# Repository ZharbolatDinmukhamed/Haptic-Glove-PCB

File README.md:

# Haptic Glove PCB

A wrist-mounted PCB for a haptic feedback glove, developed as part of my Research Assistantship at the Tactile Laboratory, Nazarbayev University.

## Overview
The board mounts on the wrist and drives 5 vibromotors, one per fingertip, delivering independent tactile feedback to each finger. It is designed to sit inside a glove, secured to the wrist via velcro straps threaded through slots in the board.

## Design Details
- **Board size:** 65mm x 50mm
- **Actuators:** 5x vibromotors (one per fingertip), each with a dedicated 3.3V power channel and signal channel
- **Driver components:** Capacitors and diodes placed near the board edge for each motor driver channel
- **Wrist-to-fingertip connection:** Discrete flexible wire harness (evaluated flex PCB / FPC, but chose a wire harness for flexibility and cost)
- **Mounting:** Component side faces outward (away from skin); board sits on the palm/volar side of the wrist inside the glove
- **Hand coverage:** Single-hand design

## Files
- `/schematic` — Schematic source files
- `/pcb` — PCB layout files
- `/gerbers` — Fabrication-ready Gerber files
- `/images` — Board renders and assembled photos
- `BOM.csv` — Bill of materials

## Tools
- [Your EDA tool — e.g. KiCad / Altium / Eagle]

## Status
[In progress / Fabricated & tested / etc. — update with current status]

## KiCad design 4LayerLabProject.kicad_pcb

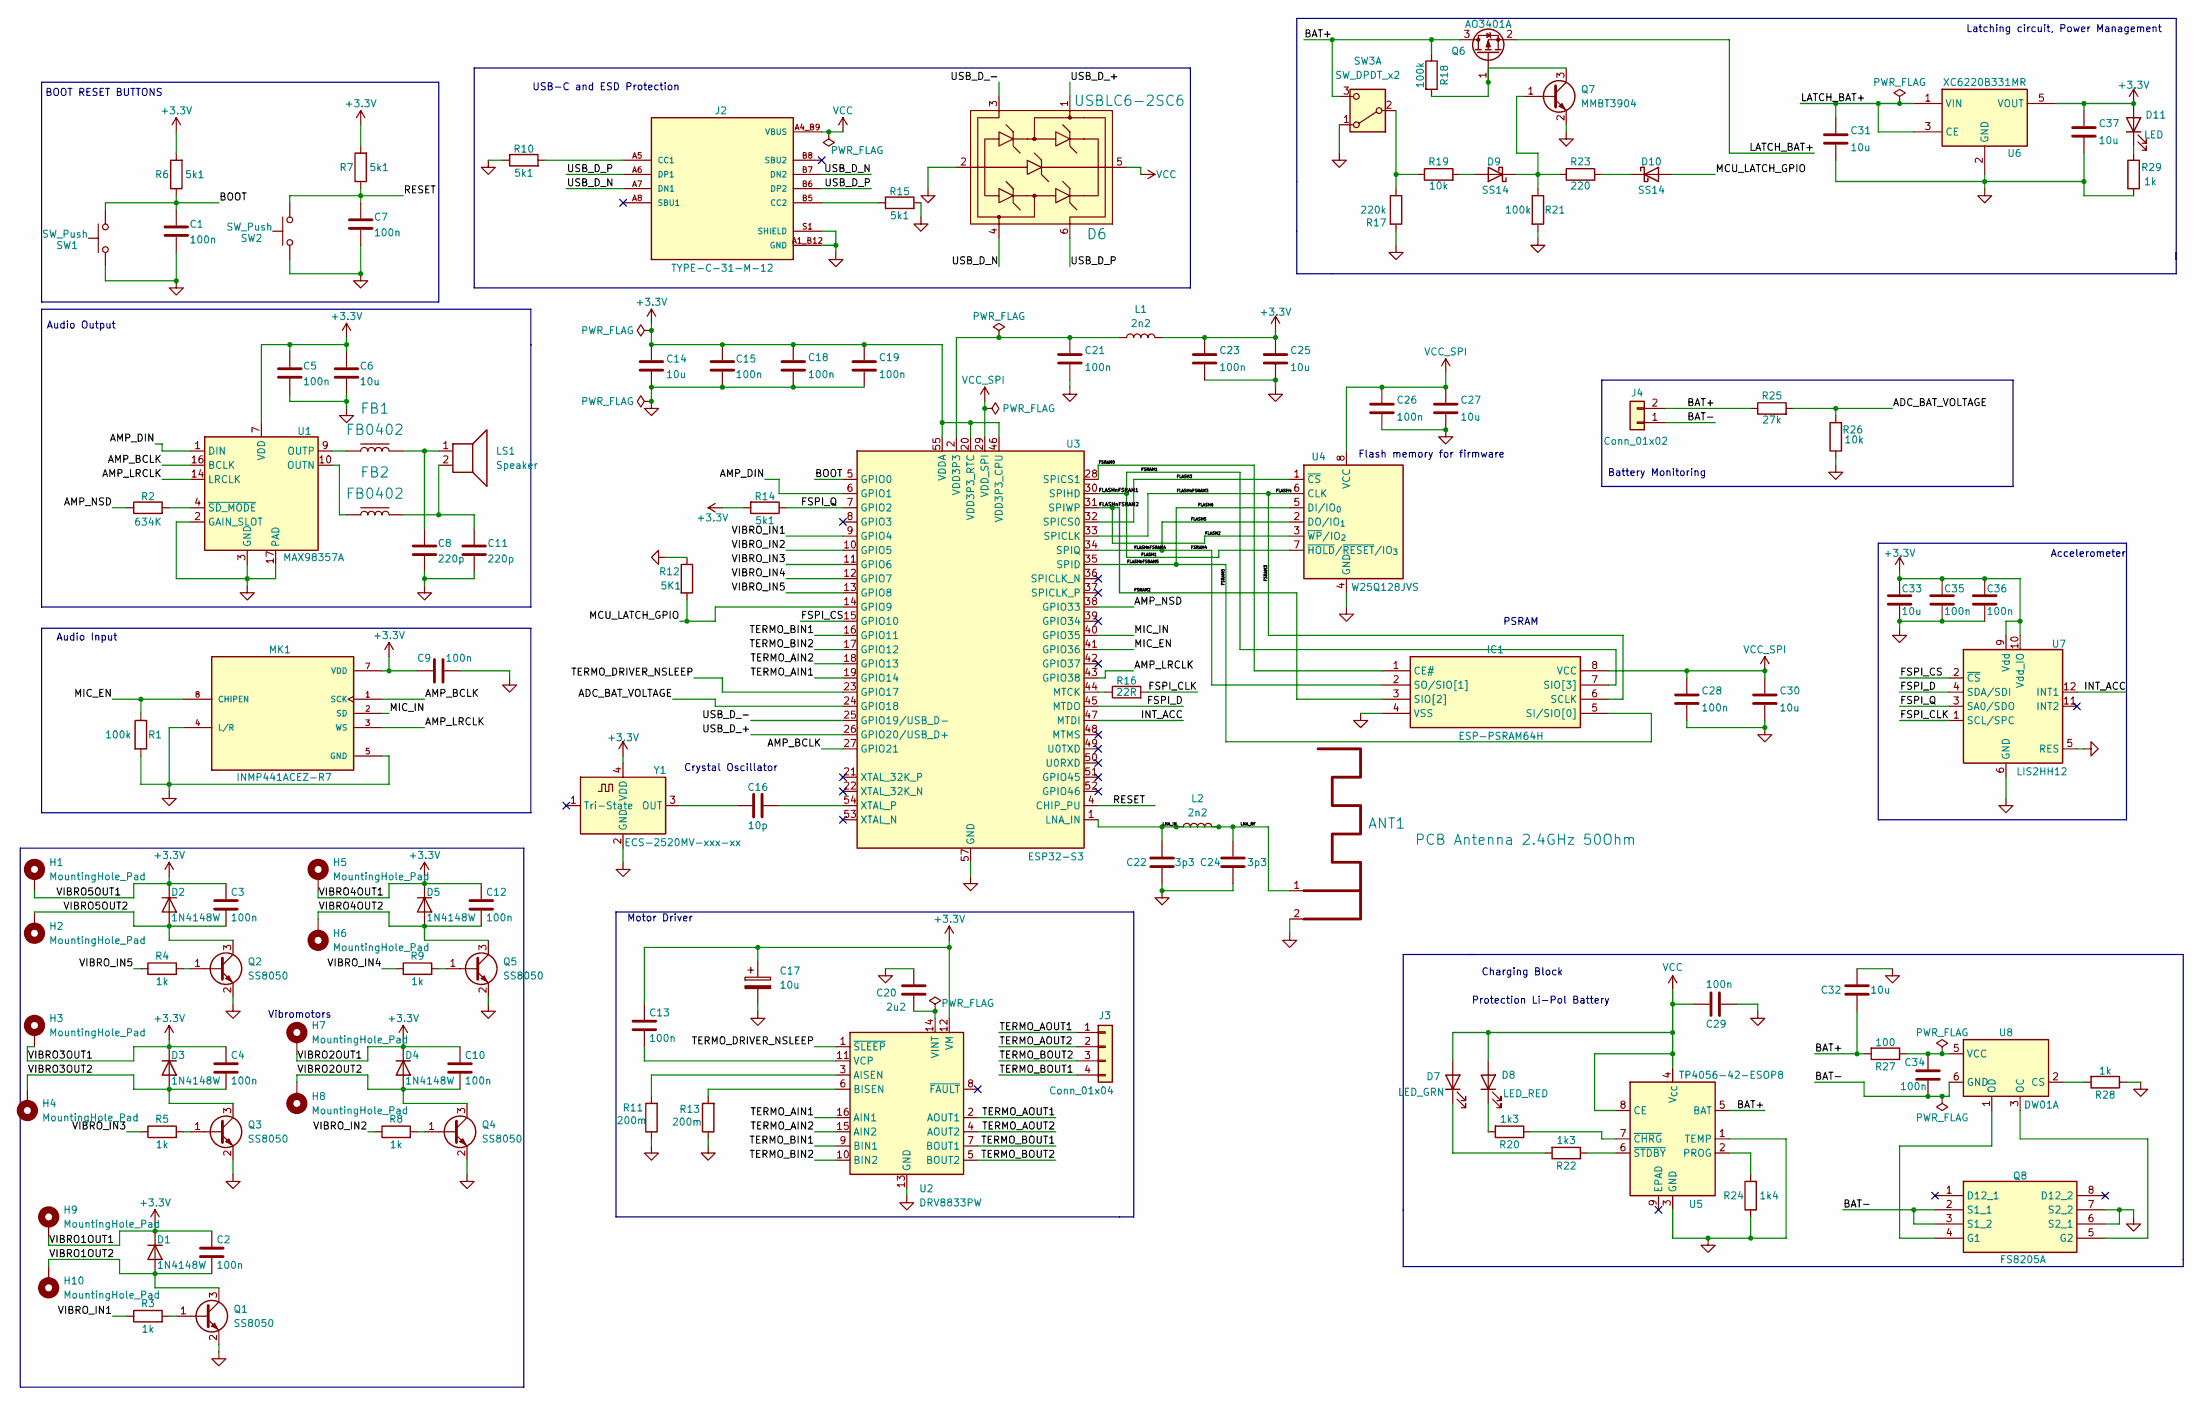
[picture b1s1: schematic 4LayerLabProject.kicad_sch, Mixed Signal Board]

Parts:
ANT1: PCB Antenna 2.4GHz 50Ohm; ANT_IFA_USB_2_4GHZ_50R
C1, C2, C3, C4, C5, C7, C9, C10, C12, C13, C15, C18, C19, C21, C23, C26, C28, C29, C34, C35, C36: 100n; C_0402_1005Metric
C6, C14, C17, C25, C27, C30, C31, C32, C33, C37: 10u; C_0603_1608Metric
C8, C11: 220p; C_0402_1005Metric
C16: 10p; C_0402_1005Metric
C20: 2u2; C_0603_1608Metric
C22, C24: 3p3; C_0402_1005Metric
D1, D2, D3, D4, D5: 1N4148W; D_SOD-123
D6: USBLC6-2SC6; SOT-23-6; Manufacturer Part Number USBLC6-2SC6
D7: LED_GRN; LED_0603_1608Metric_Pad1.05x0.95mm_HandSolder
D8: LED_RED; LED_0603_1608Metric_Pad1.05x0.95mm_HandSolder
D9, D10: SS14; D_SMA
D11: LED; LED_0603_1608Metric_Pad1.05x0.95mm_HandSolder
FB1, FB2: FB0402; FB_0402; Manufacturer Part Number *; LCSC *
H1, H2, H3, H4, H5, H6, H7, H8, H9, H10: MountingHole_Pad; tht_pad
IC1: ESP-PSRAM64H; SOIC127P600X175-8N; Manufacturer_Part_Number ESP-PSRAM64H
J2: TYPE-C-31-M-12; HRO_TYPE-C-31-M-12; PARTREV 2020.12.08
J3: Conn_01x04; Molex_PicoBlade_53048-0410_1x04_P1.25mm_Horizontal
J4: Conn_01x02; Molex_PicoBlade_53048-0210_1x02_P1.25mm_Horizontal
L1, L2: 2n2; L_0402_1005Metric
LS1: Speaker; Untitled_1
MK1: INMP441ACEZ-R7; MIC_INMP441ACEZ-R7; PARTREV 1.1
Q1, Q2, Q3, Q4, Q5: SS8050; SOT-23
Q6: AO3401A; SOT-23
Q7: MMBT3904; SOT-23
Q8: FS8205A; SOP65P640X120-8N; Manufacturer_Part_Number FS8205A
R1, R18, R21: 100k; R_0402_1005Metric
R2: 634K; R_0805_2012Metric
R3, R4, R5, R8, R9, R28, R29: 1k; R_0402_1005Metric
R6, R7, R10, R14, R15: 5k1; R_0402_1005Metric
R11, R13: 200m; R_0603_1608Metric
R12: 5K1; R_0402_1005Metric
R16: 22R; R_0402_1005Metric
R17: 220k; R_0402_1005Metric
R19, R26: 10k; R_0402_1005Metric
R20, R22: 1k3; R_0402_1005Metric
R23: 220; R_0402_1005Metric
R24: 1k4; R_0402_1005Metric
R25: 27k; R_0402_1005Metric
R27: 100; R_0402_1005Metric
SW1, SW2: SW_Push; SW_Push_SPST_NO_Alps_SKRK
SW3: SW_DPDT_x2; OS102011MA1QN1
U1: MAX98357A; TQFN-16-1EP_3x3mm_P0.5mm_EP1.23x1.23mm
U2: DRV8833PW; TSSOP-16_4.4x5mm_P0.65mm
U3: ESP32-S3; QFN56_7X7_EXP
U4: W25Q128JVS; SOIC-8_5.3x5.3mm_P1.27mm
U5: TP4056-42-ESOP8; SOIC-8-1EP_3.9x4.9mm_P1.27mm_EP2.41x3.3mm_ThermalVias
U6: XC6220B331MR; SOT-23-5
U7: LIS2HH12; LGA-12_2x2mm_P0.5mm
U8: DW01A; SOT-23-6
Y1: ECS-2520MV-xxx-xx; Oscillator_SMD_ECS_2520MV-xxx-xx-4Pin_2.5x2.0mm

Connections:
+3.3V: C2.1, C3.1, C4.1, C5.1, C6.1, C9.1, C10.1, C12.1, C13.1, C14.1, C15.1, C17.1, C18.1, C19.1, C23.1, C25.1, C33.1, C35.1, C36.1, C37.1, D1.1 (K), D2.1 (K), D3.1 (K), D4.1 (K), D5.1 (K), D11.2 (A), H1.1 (1_1), H3.1 (1_1), H5.1 (1_1), H7.1 (1_1), H9.1 (1_1), L1.2, MK1.7 (VDD), R6.2, R7.2, R14.2, U1.7 (VDD), U1.8 (VDD), U2.12 (VM), U3.20 (VDD3P3_RTC), U3.46 (VDD3P3_CPU), U3.55 (VDDA), U3.56 (VDDA), U6.5 (VOUT), U7.9 (Vdd), U7.10 (Vdd_IO), Y1.4 (VDD)
/ADC_BAT_VOLTAGE: R25.2, R26.2, U3.24 (GPIO18)
/AMP_BCLK: MK1.1 (SCK), U1.16 (BCLK), U3.27 (GPIO21)
/AMP_DIN: U1.1 (DIN), U3.6 (GPIO1)
/AMP_LRCLK: MK1.3 (WS), U1.14 (LRCLK), U3.43 (GPIO38)
/AMP_NSD: R2.1, U3.38 (GPIO33)
/BAT+: C32.2, J4.2, Q6.3 (D), R18.1, R25.1, R27.2, SW3.3 (C), U5.5 (BAT)
/BAT-: C34.2, J4.1, Q8.2 (S1_1), Q8.3 (S1_2), U8.6 (GND)
/BOOT: C1.1, R6.1, SW1.2, U3.5 (GPIO0)
/FLASH1: IC1.7 (SIO[3]), U3.30 (SPIHD), U4.7 (~HOLD/~RESET/IO_{3})
/FLASH2: IC1.3 (SIO[2]), U3.31 (SPIWP), U4.3 (~WP/IO_{2})
/FLASH3: U3.32 (SPICS0), U4.1 (~CS)
/FLASH4: IC1.6 (SCLK), U3.33 (SPICLK), U4.6 (CLK)
/FLASH5: IC1.2 (SO/SIO[1]), U3.34 (SPIQ), U4.2 (DO/IO_{1})
/FLASH6: IC1.5 (SI/SIO[0]), U3.35 (SPID), U4.5 (DI/IO_{0})
/FSPI_CLK: R16.2, U7.1 (SCL/SPC)
/FSPI_CS: U3.15 (GPIO10), U7.2 (~CS)
/FSPI_D: U3.45 (MTDO), U7.4 (SDA/SDI)
/FSPI_Q: R14.1, U3.7 (GPIO2), U7.3 (SA0/SDO)
/FSRAM0: IC1.1 (CE#), U3.28 (SPICS1)
/INT_ACC: U3.47 (MTDI), U7.12 (INT1)
/LATCH_BAT+: C31.1, Q6.2 (S), U6.1 (VIN), U6.3 (CE)
/LNA_IN: ANT1.1 (RF), C22.2, C24.2, L2.1, L2.2, U3.1 (LNA_IN)
/MCU_LATCH_GPIO: D10.2 (A), R12.2, U3.14 (GPIO9)
/MIC_EN: MK1.8 (CHIPEN), R1.1, U3.41 (GPIO36)
/MIC_IN: MK1.2 (SD), U3.40 (GPIO35)
/RESET: C7.1, R7.1, SW2.2, U3.4 (CHIP_PU)
/TERMO_AIN1: U2.16 (AIN1), U3.19 (GPIO14)
/TERMO_AIN2: U2.15 (AIN2), U3.18 (GPIO13)
/TERMO_AOUT1: J3.1, U2.2 (AOUT1)
/TERMO_AOUT2: J3.2, U2.4 (AOUT2)
/TERMO_BIN1: U2.9 (BIN1), U3.16 (GPIO11)
/TERMO_BIN2: U2.10 (BIN2), U3.17 (GPIO12)
/TERMO_BOUT1: J3.4, U2.7 (BOUT1)
/TERMO_BOUT2: J3.3, U2.5 (BOUT2)
/TERMO_DRIVER_NSLEEP: U2.1 (~SLEEP), U3.23 (GPIO17)
/USB_D_+: D6.1 (IO1), U3.26 (GPIO20/USB_D+)
/USB_D_-: D6.3 (IO2), U3.25 (GPIO19/USB_D-)
/USB_D_N: D6.4 (IO2), J2.A7 (DN1), J2.B7 (DN2)
/USB_D_P: D6.6 (IO1), J2.A6 (DP1), J2.B6 (DP2)
/VIBRO1OUT2: C2.2, D1.2 (A), H10.1 (1_1), Q1.3 (C)
/VIBRO2OUT2: C10.2, D4.2 (A), H8.1 (1_1), Q4.3 (C)
/VIBRO3OUT2: C4.2, D3.2 (A), H4.1 (1_1), Q3.3 (C)
/VIBRO4OUT2: C12.2, D5.2 (A), H6.1 (1_1), Q5.3 (C)
/VIBRO5OUT2: C3.2, D2.2 (A), H2.1 (1_1), Q2.3 (C)
/VIBRO_IN1: R3.1, U3.9 (GPIO4)
/VIBRO_IN2: R8.1, U3.10 (GPIO5)
/VIBRO_IN3: R5.1, U3.11 (GPIO6)
/VIBRO_IN4: R9.1, U3.12 (GPIO7)
/VIBRO_IN5: R4.1, U3.13 (GPIO8)
GND: ANT1.2 (GND), C1.2, C5.2, C6.2, C7.2, C8.2, C9.2, C11.2, C14.2, C15.2, C17.2, C18.2, C19.2, C20.1, C21.2, C22.1, C23.2, C24.1, C25.2, C26.2, C27.2, C28.2, C29.1, C30.2, C31.2, C32.1, C33.2, C35.2, C36.2, C37.2, D6.2 (GND), IC1.4 (VSS), J2.A1_B12 (GND), J2.B1_A12 (GND), J2.S1 (SHIELD), J2.S2 (SHIELD), J2.S3 (SHIELD), J2.S4 (SHIELD), MK1.4 (L/R), MK1.5 (GND), MK1.6 (GND), MK1.9 (GND), Q1.2 (E), Q2.2 (E), Q3.2 (E), Q4.2 (E), Q5.2 (E), Q7.2 (E), Q8.6 (S2_1), Q8.7 (S2_2), R1.2, R10.1, R11.1, R12.1, R13.1, R15.2, R17.2, R21.2, R24.1, R26.1, R28.1, R29.2, SW1.1, SW2.1, SW3.1 (A), U1.2 (GAIN_SLOT), U1.3 (GND), U1.11 (GND), U1.15 (GND), U1.17 (PAD), U2.13 (GND), U3.57 (GND), U4.4 (GND), U5.1 (TEMP), U5.3 (GND), U6.2 (GND), U7.5 (RES), U7.6 (GND), U7.7 (GND), U7.8 (GND), Y1.2 (GND)
unnamed: C8.1, FB1.2, LS1.1
unnamed: C11.1, FB2.2, LS1.2
unnamed: C21.1, L1.1, U3.2 (VDD3P3), U3.3 (VDD3P3)
unnamed: D7.1 (K), R22.2
unnamed: D8.1 (K), R20.2
unnamed: D9.2 (A), R19.2
unnamed: D9.1 (K), Q7.1 (B), R21.1, R23.1
unnamed: D10.1 (K), R23.2
unnamed: D11.1 (K), R29.1
unnamed: J2.A5 (CC1), R10.2
unnamed: J2.B5 (CC2), R15.1
unnamed: Q1.1 (B), R3.2
unnamed: Q2.1 (B), R4.2
unnamed: Q3.1 (B), R5.2
unnamed: Q4.1 (B), R8.2
unnamed: Q5.1 (B), R9.2
unnamed: Q6.1 (G), Q7.3 (C), R18.2
unnamed: Q8.4 (G1), U8.1 (OD)
unnamed: Q8.5 (G2), U8.3 (OC)
unnamed: R17.1, R19.1, SW3.2 (B)
unnamed: FB2.1, U1.10 (OUTN)
unnamed: FB1.1, U1.9 (OUTP)
unnamed: R2.2, U1.4 (~SD_MODE)
unnamed: R11.2, U2.3 (AISEN)
unnamed: R13.2, U2.6 (BISEN)
unnamed: C13.2, U2.11 (VCP)
unnamed: C20.2, U2.14 (VINT)
unnamed: R16.1, U3.44 (MTCK)
unnamed: C16.2, U3.54 (XTAL_P)
unnamed: R24.2, U5.2 (PROG)
unnamed: R20.1, U5.7 (~CHRG)
unnamed: R22.1, U5.6 (~STDBY)
unnamed: R28.2, U8.2 (CS)
unnamed: C34.1, R27.1, U8.5 (VCC)
unnamed: C16.1, Y1.3 (OUT)
VCC: C29.2, D6.5 (VBUS), D7.2 (A), D8.2 (A), J2.A4_B9 (VBUS), J2.B4_A9 (VBUS), U5.4 (V_{CC}), U5.8 (CE)
VCC_SPI: C26.1, C27.1, C28.1, C30.1, IC1.8 (VCC), U3.29 (VDD_SPI), U4.8 (VCC)

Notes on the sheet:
Accelerometer
Charging Block
Battery Monitoring
USB-C and ESD Protection
Vibromotors
BOOT RESET BUTTONS
Flash memory for firmware
Crystal Oscillator
Audio Input
PSRAM
Latching circuit, Power Management
Motor Driver
Audio Output
Protection Li-Pol Battery

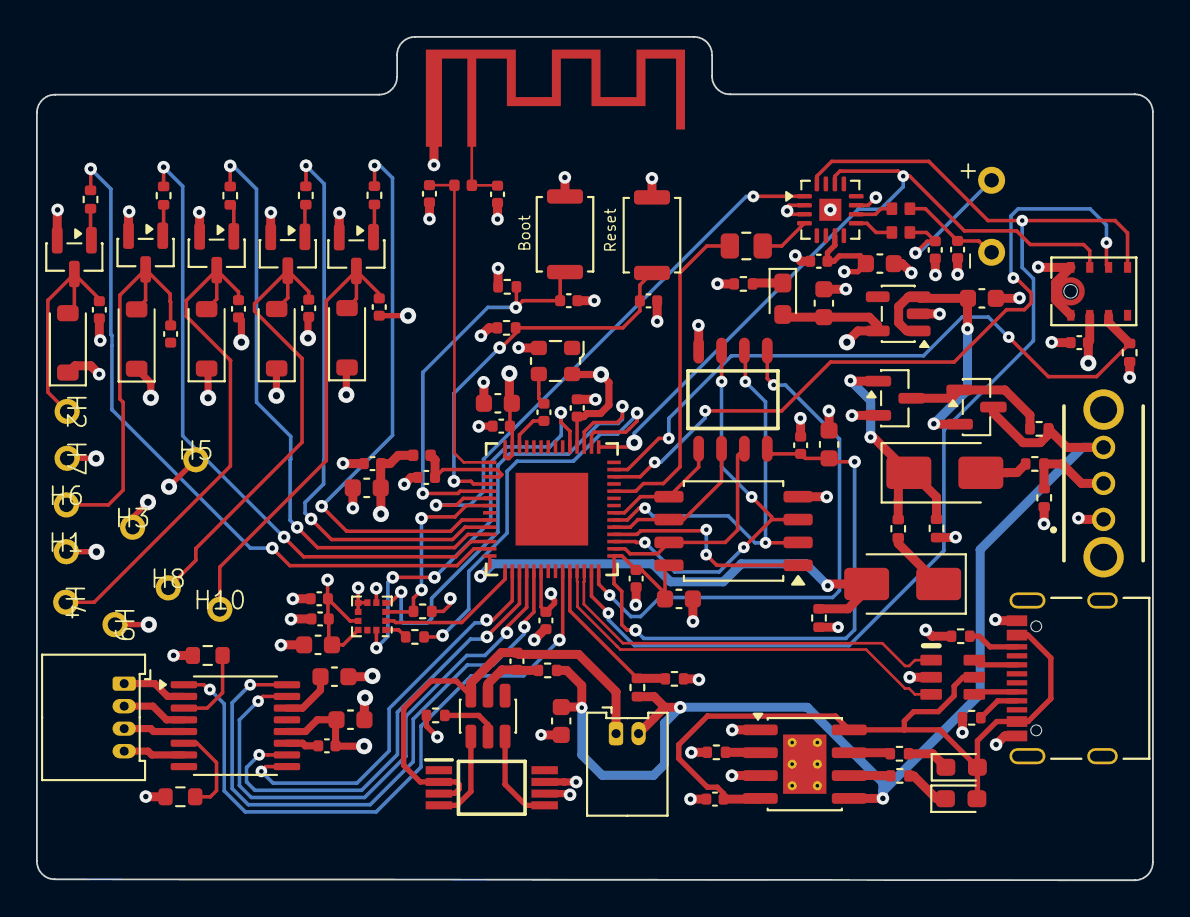
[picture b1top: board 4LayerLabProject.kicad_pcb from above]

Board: 4 copper layers, 62.0 x 46.9 mm, 118 parts (0 on the bottom side), 88 nets.
